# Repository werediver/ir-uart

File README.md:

# IR UART

This is an IR UART adapter. Its transmitter and receiver are independent, there is no automatic echo suppression. The receiver is based on [TSDP34156](http://www.vishay.com/docs/82667/tsdp341.pdf) IR receiver. The transmitter is built using [TSAL6400](https://www.vishay.com/docs/81011/tsal6400.pdf) 940 nm IR LEDs and a carrier generator based on [74HC132](https://assets.nexperia.com/documents/data-sheet/74HC_HCT132.pdf) quad-NAND CMOS gate.

The nominal transmission rate is 9600 baud. The carrier generator should be tuned to 57.6 kHz (with 6 cycles per bit it gives $57600 / 6 = 9600$ baud).

The adapter can be powered from 3.3 V or 5 V and will operate with the corresponding logic levels.

The board size is just 21x36 mm and provides 8 unconnected PTH (plated through holes) for mounting purposes. It should fit the [Pico (RP2040)](https://datasheets.raspberrypi.com/pico/pico-datasheet.pdf) board well.

| · | · |
| - | - |
|  |  |
|  |  |

## Performance

With minor adjustments after the first tests, the modules work as expected transmitting and receiving 1 kHz test signal. Using the modules with UART hasn't been tested yet.

Some more photos and/or info may be found at [hackaday.io/project/195022-ir-uart](https://hackaday.io/project/195022-ir-uart).

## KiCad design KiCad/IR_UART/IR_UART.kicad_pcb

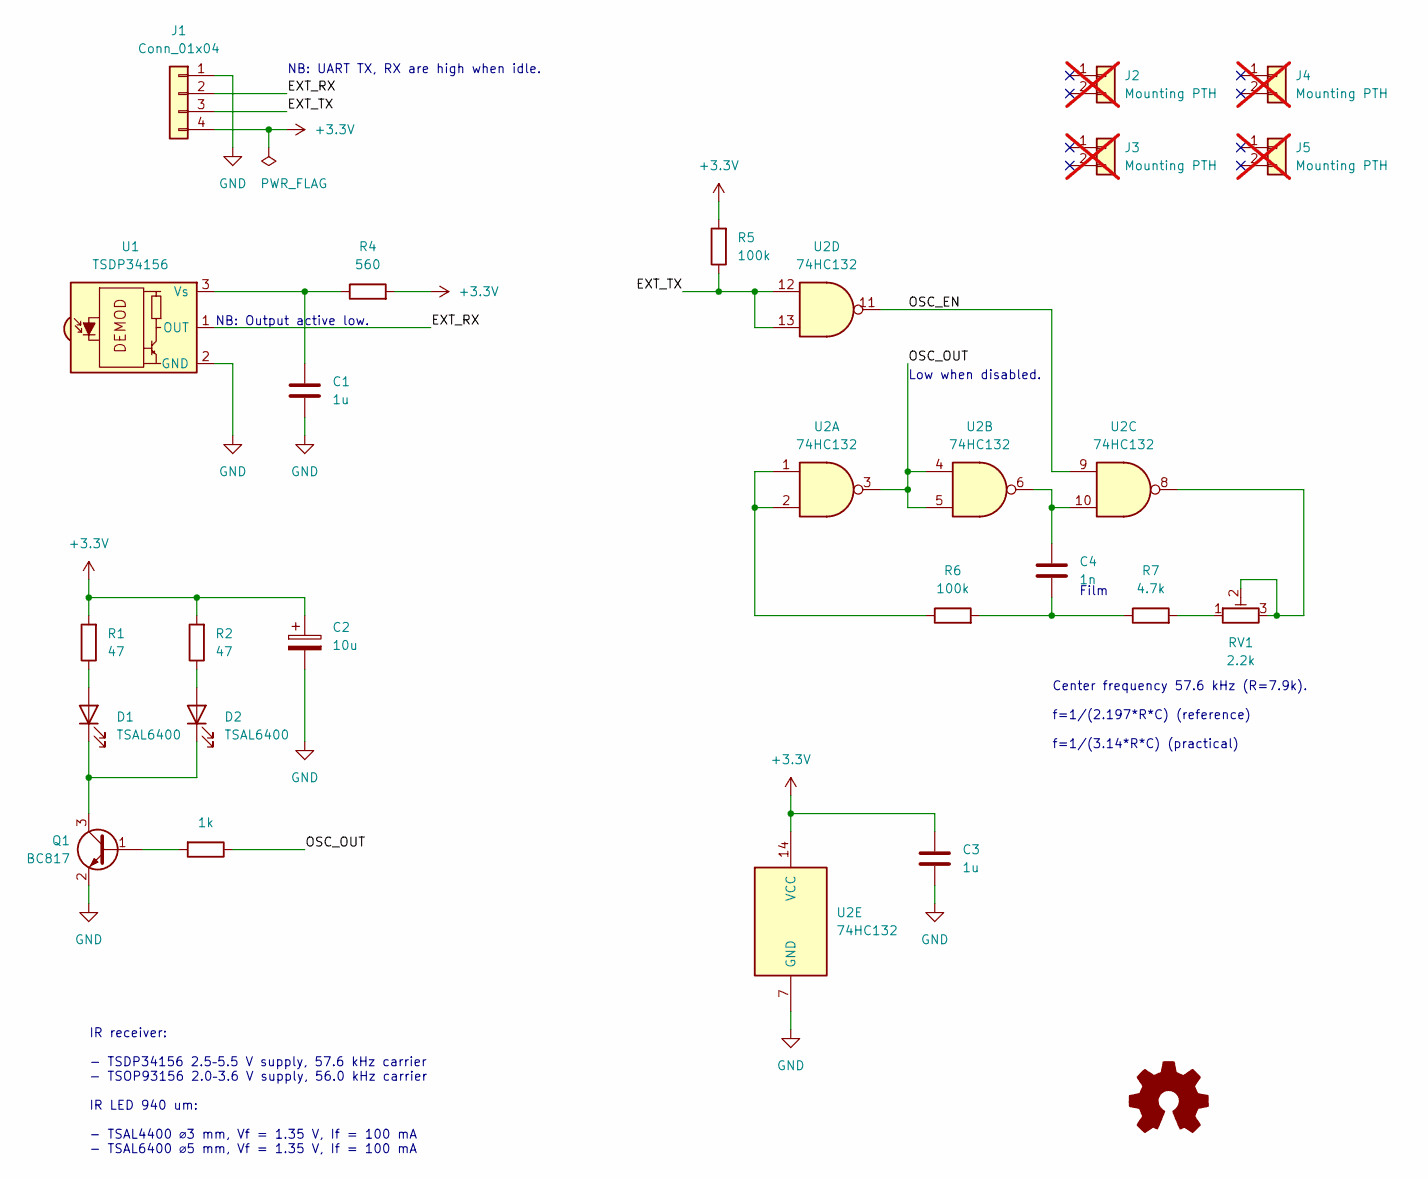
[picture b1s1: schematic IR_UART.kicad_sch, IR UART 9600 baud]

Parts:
C1, C3: 1u; C_0805_2012Metric
C2: 10u; CP_Radial_D5.0mm_P2.00mm
C4: 1n; C_Rect_L7.2mm_W2.5mm_P5.00mm_FKS2_FKP2_MKS2_MKP2
D1, D2: TSAL6400; LED_D5.0mm
J1: Conn_01x04; PinHeader_1x04_P2.54mm_Vertical
J2, J3, J4, J5: Mounting PTH; PinHeader_1x02_P2.54mm_Vertical; not fitted
Q1: BC817; SOT-23
R1, R2: 47; R_0805_2012Metric
R3: 1k; R_0805_2012Metric
R4: 560; R_0805_2012Metric
R5, R6: 100k; R_0805_2012Metric
R7: 4.7k; R_0805_2012Metric
RV1: 2.2k; Potentiometer_Bourns_3006P_Horizontal
SYM1: Logo_Open_Hardware_Small; OSHW-Logo_5.7x6mm_SilkScreen
U1: TSDP34156; Vishay_MOLD-3Pin
U2: 74HC132; SO-14_3.9x8.65mm_P1.27mm

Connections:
+3.3V: C2.1, C3.1, J1.4, R1.2, R2.2, R4.2, R5.2, U2.14 (VCC)
/EXT_RX: J1.2, U1.1 (OUT)
/EXT_TX: J1.3, R5.1, U2.12, U2.13
/OSC_EN: U2.9, U2.11
/OSC_OUT: R3.1, U2.3, U2.4, U2.5
GND: C1.2, C2.2, C3.2, J1.1, Q1.2 (E), U1.2 (GND), U2.7 (GND)
unnamed: C4.1, U2.6, U2.10
unnamed: C4.2, R6.2, R7.1
unnamed: D1.2 (A), R1.1
unnamed: D1.1 (K), D2.1 (K), Q1.3 (C)
unnamed: D2.2 (A), R2.1
unnamed: Q1.1 (B), R3.2
unnamed: R6.1, U2.1, U2.2
unnamed: R7.2, RV1.1
unnamed: RV1.2, RV1.3, U2.8
unnamed: C1.1, R4.1, U1.3 (Vs)

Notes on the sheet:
NB: Output active low.
Film
Low when disabled.
NB: UART TX, RX are high when idle.
Center frequency 57.6 kHz (R=7.9k). f=1/(2.197*R*C) (reference) f=1/(3.14*R*C) (practical)
IR receiver: - TSDP34156 2.5–5.5 V supply, 57.6 kHz carrier - TSOP93156 2.0–3.6 V supply, 56.0 kHz carrier IR LED 940 um: - TSAL4400 ⌀3 mm, Vf = 1.35 V, If = 100 mA - TSAL6400 ⌀5 mm, Vf = 1.35 V, If = 100 mA

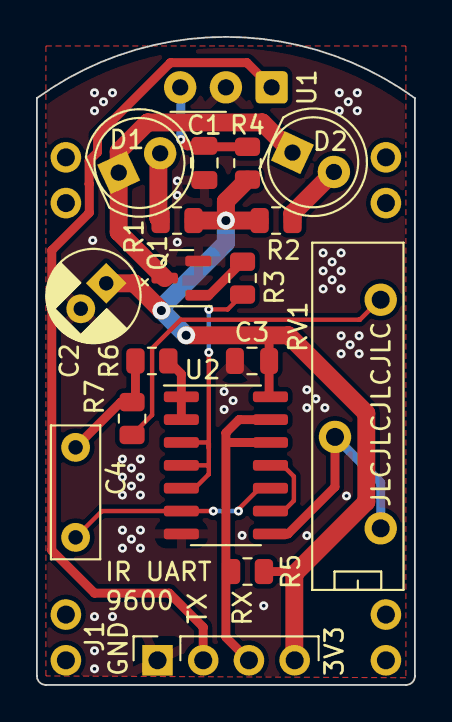
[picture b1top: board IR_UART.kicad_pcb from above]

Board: 2 copper layers, 21.0 x 36.0 mm, 23 parts (1 on the bottom side), 16 nets.

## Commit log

2024-02-24 The initial revision
2024-02-24 Add CERN-OHL-P-2.0 license
2024-03-13 Update the README
2024-03-13 Update the schematic and the PCB
    - Use 4.7k resistor instead of 6.8k in the timing circuit
    - Minor changes to the board, mainly aroung the 4-pin connector
2024-03-24 Update the schematic to specify IR receiver supply filter to be 100R 4.7uF to fix the slow fronts of the received signal.
2024-03-24 Update README and images to correspond to rev. 1.1.
